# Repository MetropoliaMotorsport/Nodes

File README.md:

# Nodes
New Power + Analog nodes for HPF24

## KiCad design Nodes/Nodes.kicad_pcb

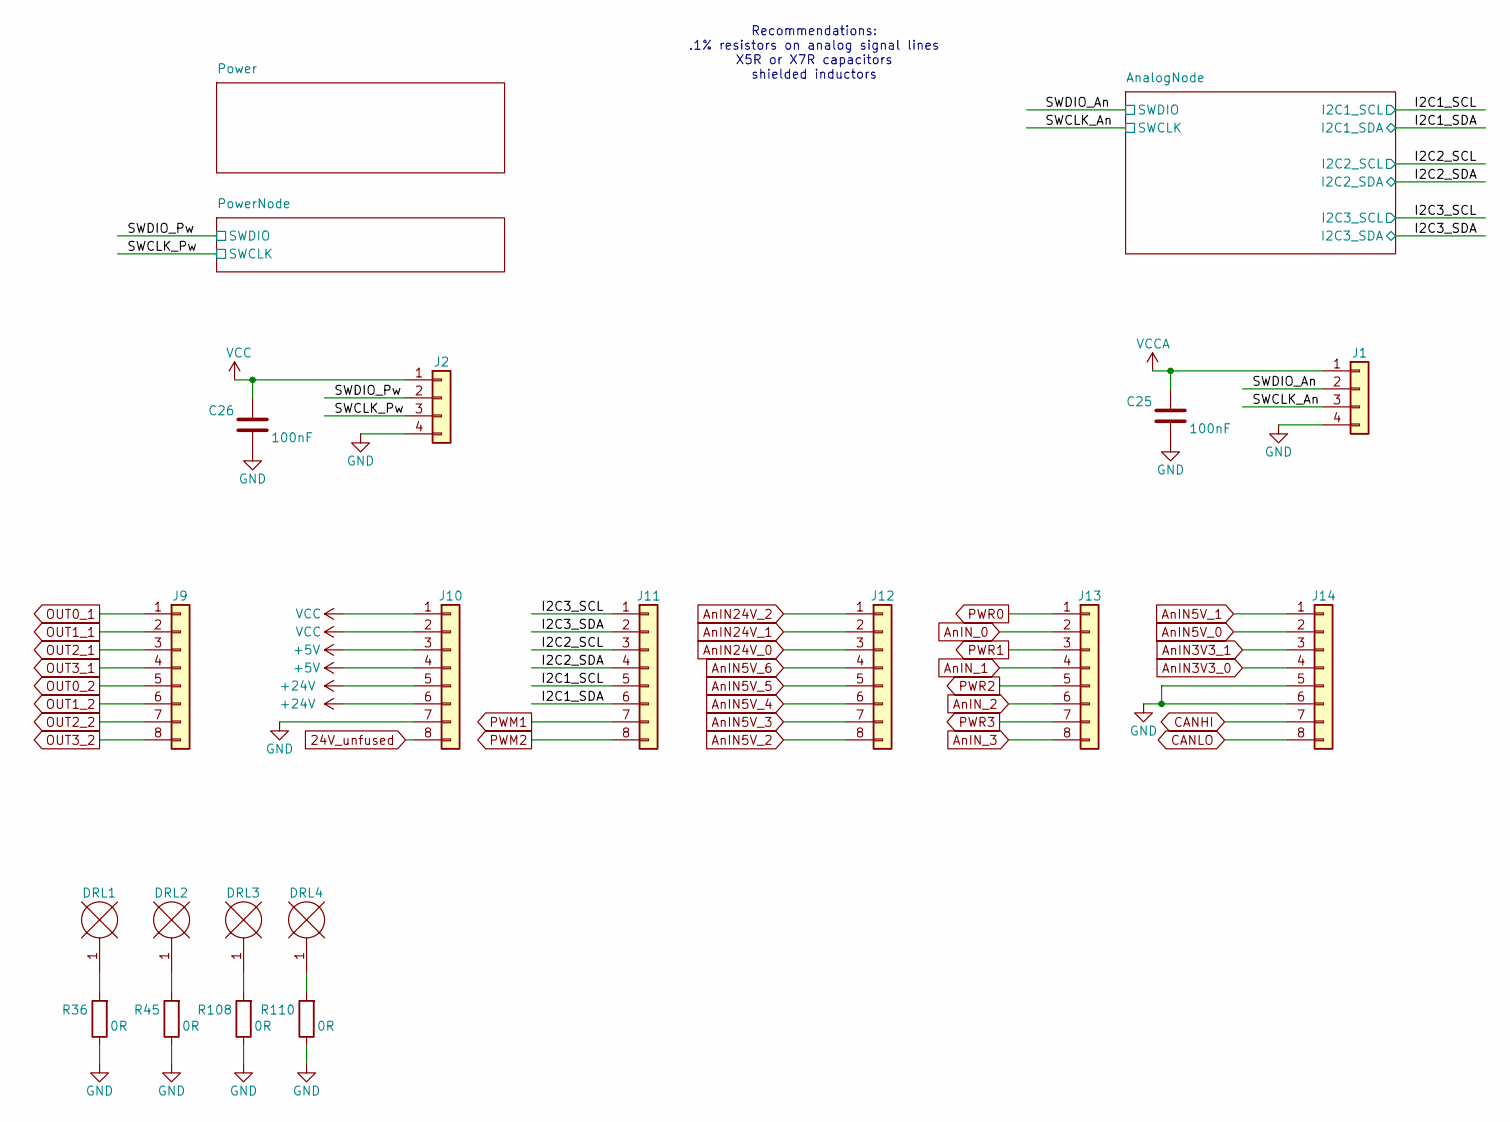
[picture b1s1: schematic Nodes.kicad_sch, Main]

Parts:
C25, C26: 100nF; C_0805_2012Metric_Pad1.18x1.45mm_HandSolder; TOLERANCE (FILL IN AS +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 10%
DRL1, DRL2, DRL3, DRL4: HOLE4.28.4; MountingHole_4.3mm_M4_Pad
J1, J2: Conn_01x04; PinSocket_1x04_P2.54mm_Vertical
J9, J10, J11, J12, J13, J14: Conn_01x08; PinHeader_1x08_P2.54mm_Vertical
R36, R45, R108, R110: 0R; R_0805_2012Metric_Pad1.20x1.40mm_HandSolder

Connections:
24V_unfused: J10.8; also elsewhere on the board
+5V: J10.3, J10.4; also elsewhere on the board
+24V: J10.5, J10.6; also elsewhere on the board
/I2C1_SCL: J11.5; also elsewhere on the board
/I2C1_SDA: J11.6; also elsewhere on the board
/I2C2_SCL: J11.3; also elsewhere on the board
/I2C2_SDA: J11.4; also elsewhere on the board
/I2C3_SCL: J11.1; also elsewhere on the board
/I2C3_SDA: J11.2; also elsewhere on the board
/SWCLK_An: J1.3; also elsewhere on the board
/SWCLK_Pw: J2.3; also elsewhere on the board
/SWDIO_An: J1.2; also elsewhere on the board
/SWDIO_Pw: J2.2; also elsewhere on the board
AnIN3V3_0: J14.4; also elsewhere on the board
AnIN3V3_1: J14.3; also elsewhere on the board
AnIN5V_0: J14.2; also elsewhere on the board
AnIN5V_1: J14.1; also elsewhere on the board
AnIN5V_2: J12.8; also elsewhere on the board
AnIN5V_3: J12.7; also elsewhere on the board
AnIN5V_4: J12.6; also elsewhere on the board
AnIN5V_5: J12.5; also elsewhere on the board
AnIN5V_6: J12.4; also elsewhere on the board
AnIN24V_0: J12.3; also elsewhere on the board
AnIN24V_1: J12.2; also elsewhere on the board
AnIN24V_2: J12.1; also elsewhere on the board
AnIN_0: J13.2; also elsewhere on the board
AnIN_1: J13.4; also elsewhere on the board
AnIN_2: J13.6; also elsewhere on the board
AnIN_3: J13.8; also elsewhere on the board
CANHI: J14.7; also elsewhere on the board
CANLO: J14.8; also elsewhere on the board
GND: C25.2, C26.2, J1.4, J2.4, J10.7, J14.5, J14.6, R36.1, R45.1, R108.1, R110.1; also elsewhere on the board
unnamed: DRL1.1, R36.2
unnamed: DRL2.1, R45.2
unnamed: DRL3.1, R108.2
unnamed: DRL4.1, R110.2
OUT0_1: J9.1; also elsewhere on the board
OUT0_2: J9.5; also elsewhere on the board
OUT1_1: J9.2; also elsewhere on the board
OUT1_2: J9.6; also elsewhere on the board
OUT2_1: J9.3; also elsewhere on the board
OUT2_2: J9.7; also elsewhere on the board
OUT3_1: J9.4; also elsewhere on the board
OUT3_2: J9.8; also elsewhere on the board
PWM1: J11.7; also elsewhere on the board
PWM2: J11.8; also elsewhere on the board
PWR0: J13.1; also elsewhere on the board
PWR1: J13.3; also elsewhere on the board
PWR2: J13.5; also elsewhere on the board
PWR3: J13.7; also elsewhere on the board
VCC: C26.1, J2.1, J10.1, J10.2; also elsewhere on the board
VCCA: C25.1, J1.1; also elsewhere on the board

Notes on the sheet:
Recommendations: .1% resistors on analog signal lines X5R or X7R capacitors shielded inductors
${REVISION}

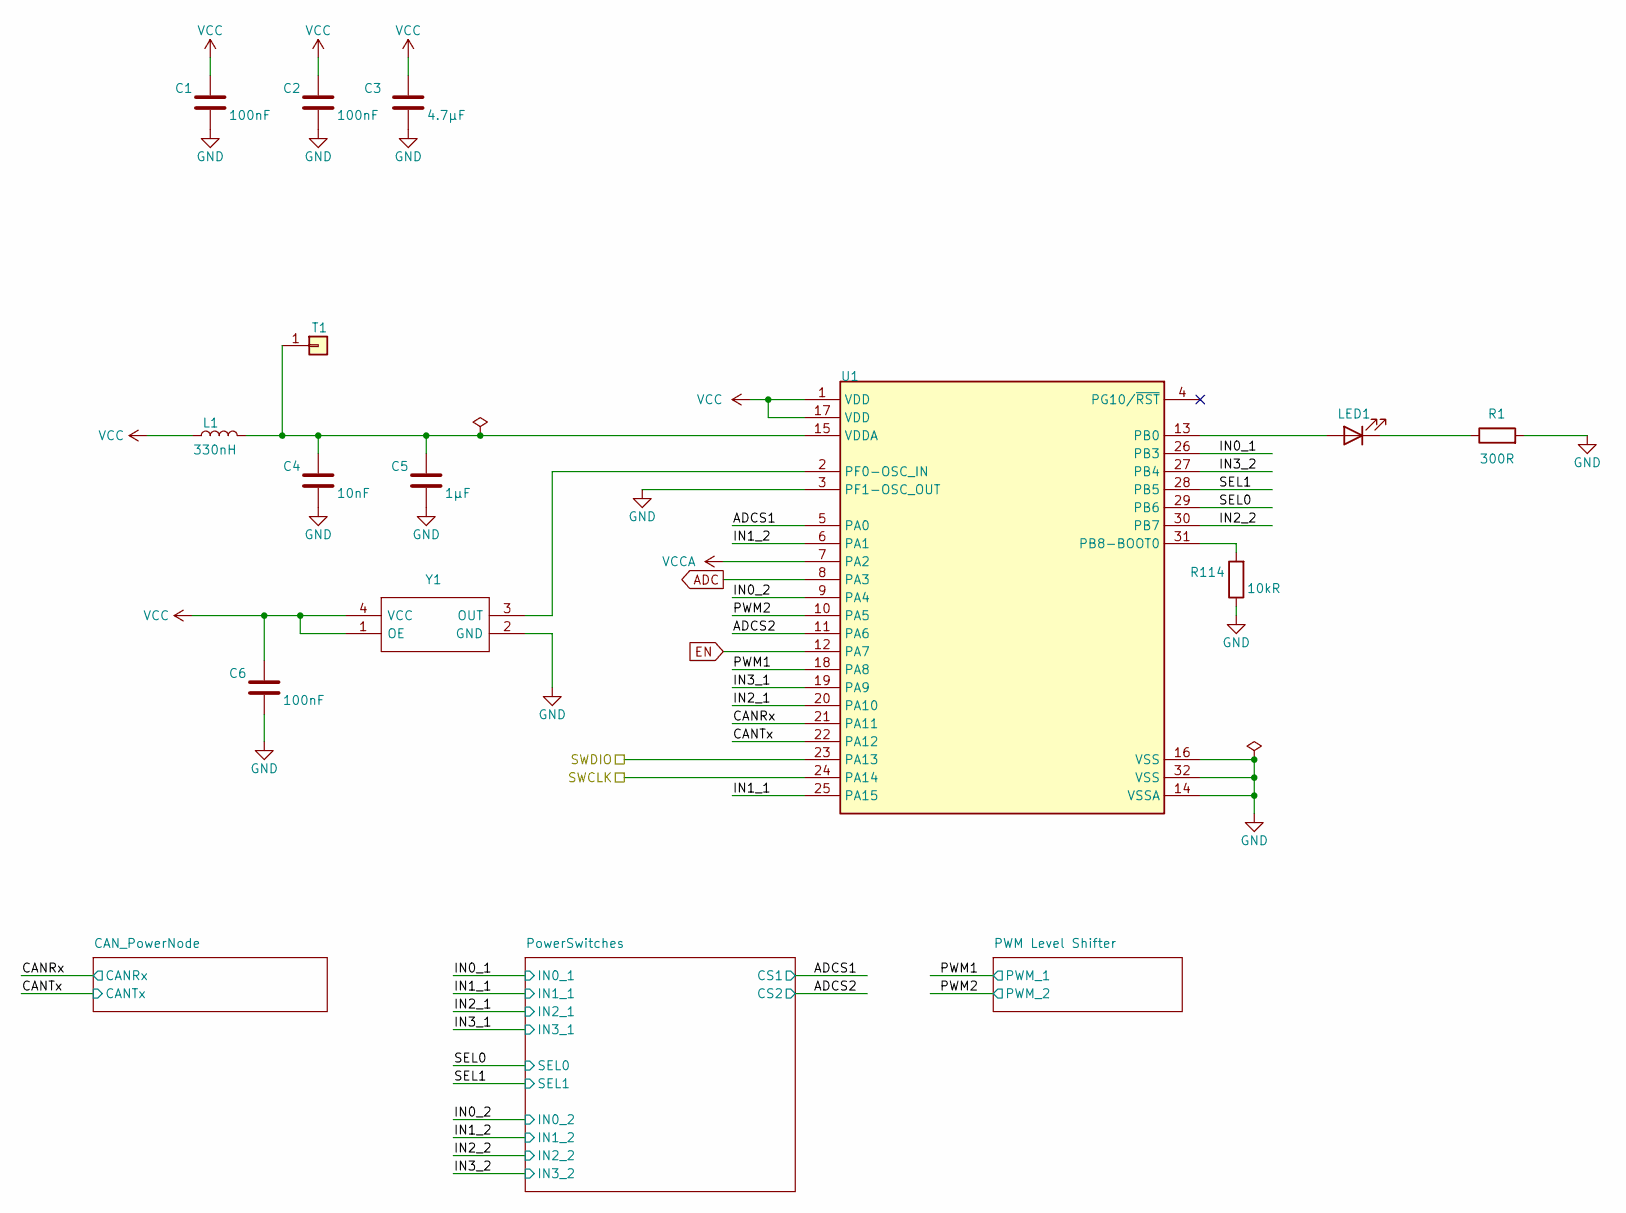
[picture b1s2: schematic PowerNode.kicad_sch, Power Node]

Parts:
C1, C2, C6: 100nF; C_0805_2012Metric_Pad1.18x1.45mm_HandSolder; TOLERANCE (FILL IN AS +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 10%
C3: 4.7µF; C_0805_2012Metric_Pad1.18x1.45mm_HandSolder; TOLERANCE (FILL IN AS +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 10%
C4: 10nF; C_0805_2012Metric_Pad1.18x1.45mm_HandSolder; TOLERANCE (FILL IN AS +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 10%
C5: 1µF; C_0805_2012Metric_Pad1.18x1.45mm_HandSolder; TOLERANCE (FILL IN AS +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 10%
L1: 330nH; L_0805_2012Metric_Pad1.15x1.40mm_HandSolder; TOLERANCE 20%
LED1: SML-210VTT86; LED_0805_2012Metric_Pad1.15x1.40mm_HandSolder; FORWARD VOLTAGE 2V; REVERSE VOLTAGE 4V; MANUFACTURER PART NUMBER SML-210VTT86; MOUSER DESCRIPTION Standard LEDs - SMD RED SMD TRANS LENS
R1: 300R; R_0805_2012Metric_Pad1.20x1.40mm_HandSolder; POWER RATING 400mW; TOLERANCE 5%
R114: 10kR; R_0805_2012Metric_Pad1.20x1.40mm_HandSolder
T1: Conn_01x01; TestPoint_THTPad_D1.5mm_Drill0.7mm
U1: STM32G431KBT6; FP-LQFP32-5V-IPC_B
Y1: SG-8018CE_8.0000M-TJHPA3; SG8018CE80000MTJHPA3; Mouser Part Number 732-CE8M-TJHPA3

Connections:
/PowerNode/ADCS1: U1.5 (PA0); also elsewhere on the board
/PowerNode/ADCS2: U1.11 (PA6); also elsewhere on the board
/PowerNode/CANRx: U1.21 (PA11); also elsewhere on the board
/PowerNode/CANTx: U1.22 (PA12); also elsewhere on the board
/PowerNode/IN0_1: U1.26 (PB3); also elsewhere on the board
/PowerNode/IN0_2: U1.9 (PA4); also elsewhere on the board
/PowerNode/IN1_1: U1.25 (PA15); also elsewhere on the board
/PowerNode/IN1_2: U1.6 (PA1); also elsewhere on the board
/PowerNode/IN2_1: U1.20 (PA10); also elsewhere on the board
/PowerNode/IN2_2: U1.30 (PB7); also elsewhere on the board
/PowerNode/IN3_1: U1.19 (PA9); also elsewhere on the board
/PowerNode/IN3_2: U1.27 (PB4); also elsewhere on the board
/PowerNode/PWM1: U1.18 (PA8); also elsewhere on the board
/PowerNode/PWM2: U1.10 (PA5); also elsewhere on the board
/PowerNode/SEL0: U1.29 (PB6); also elsewhere on the board
/PowerNode/SEL1: U1.28 (PB5); also elsewhere on the board
/SWCLK_Pw: U1.24 (PA14); also elsewhere on the board
/SWDIO_Pw: U1.23 (PA13); also elsewhere on the board
ADC: U1.8 (PA3); also elsewhere on the board
EN: U1.12 (PA7); also elsewhere on the board
GND: C1.2, C2.2, C3.2, C4.2, C5.2, C6.2, R1.2, R114.1, U1.3 (PF1-OSC_OUT), U1.14 (VSSA), U1.16 (VSS), U1.32 (VSS), Y1.2 (GND); also elsewhere on the board
unnamed: LED1.2 (A), U1.13 (PB0)
unnamed: LED1.1 (K), R1.1
unnamed: C4.1, C5.1, L1.2, T1.1, U1.15 (VDDA)
unnamed: R114.2, U1.31 (PB8-BOOT0)
unnamed: U1.2 (PF0-OSC_IN), Y1.3 (OUT)
VCC: C1.1, C2.1, C3.1, C6.1, L1.1, U1.1 (VDD), U1.17 (VDD), Y1.1 (OE), Y1.4 (VCC); also elsewhere on the board
VCCA: U1.7 (PA2); also elsewhere on the board

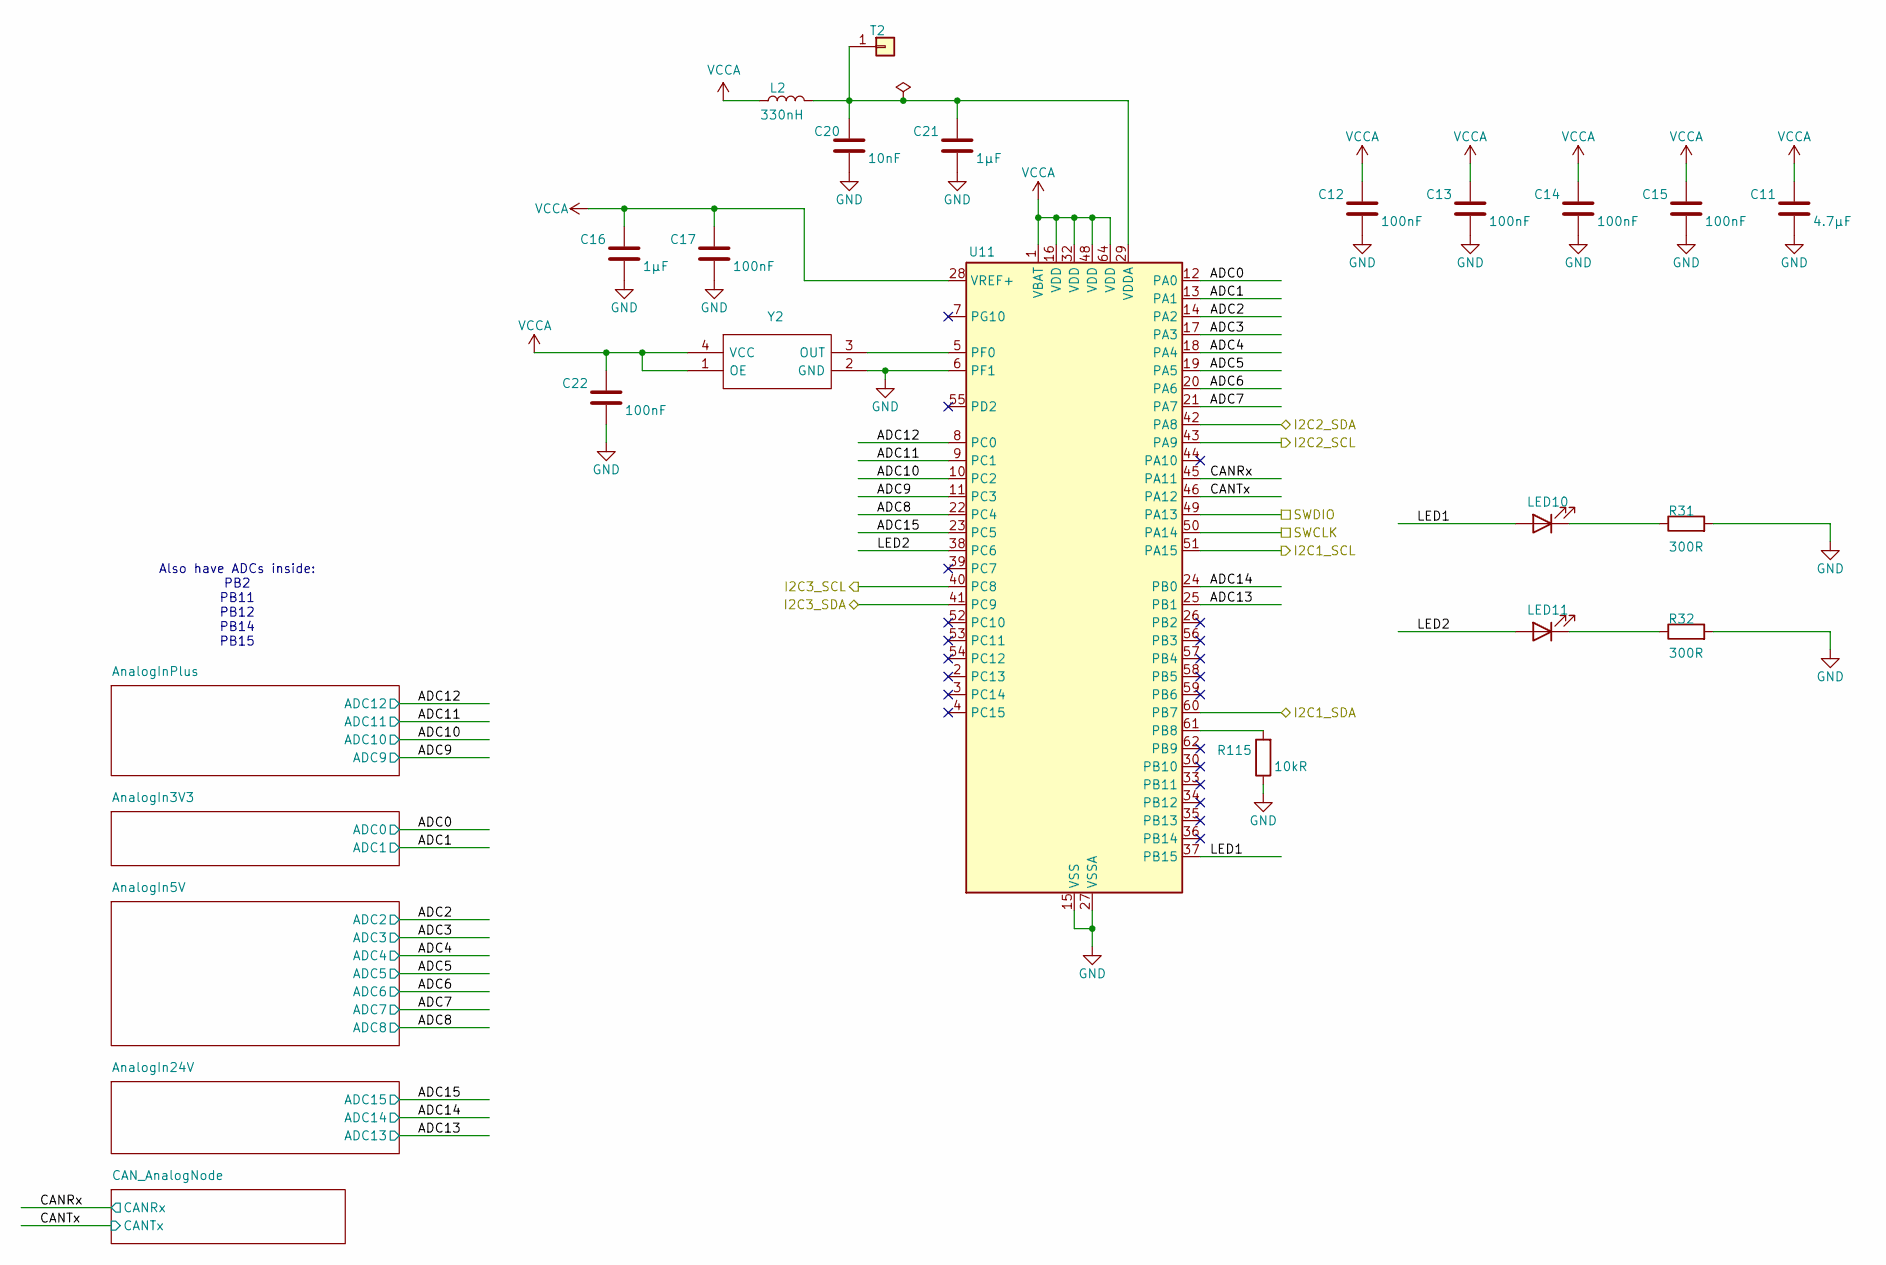
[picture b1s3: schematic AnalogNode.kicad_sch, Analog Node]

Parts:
C11: 4.7µF; C_0805_2012Metric_Pad1.18x1.45mm_HandSolder; TOLERANCE (FILL IN AS +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 10%
C12, C13, C14, C15, C17, C22: 100nF; C_0805_2012Metric_Pad1.18x1.45mm_HandSolder; TOLERANCE (FILL IN AS +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 10%
C16, C21: 1µF; C_0805_2012Metric_Pad1.18x1.45mm_HandSolder; TOLERANCE (FILL IN AS +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 10%
C20: 10nF; C_0805_2012Metric_Pad1.18x1.45mm_HandSolder; TOLERANCE (FILL IN AS +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 10%
L2: 330nH; L_0805_2012Metric_Pad1.15x1.40mm_HandSolder; TOLERANCE 20%
LED10, LED11: SML-210VTT86; LED_0805_2012Metric_Pad1.15x1.40mm_HandSolder; FORWARD VOLTAGE 2V; REVERSE VOLTAGE 4V; MANUFACTURER PART NUMBER SML-210VTT86; MOUSER DESCRIPTION Standard LEDs - SMD RED SMD TRANS LENS
R31, R32: 300R; R_0805_2012Metric_Pad1.20x1.40mm_HandSolder; POWER RATING 400mW; TOLERANCE 5%
R115: 10kR; R_0805_2012Metric_Pad1.20x1.40mm_HandSolder
T2: Conn_01x01; TestPoint_THTPad_D1.5mm_Drill0.7mm
U11: STM32G431RBTx; LQFP-64_10x10mm_P0.5mm
Y2: SG-8018CE_8.0000M-TJHPA3; SG8018CE80000MTJHPA3; Mouser Part Number 732-CE8M-TJHPA3

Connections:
/AnalogNode/ADC0: U11.12 (PA0); also elsewhere on the board
/AnalogNode/ADC1: U11.13 (PA1); also elsewhere on the board
/AnalogNode/ADC2: U11.14 (PA2); also elsewhere on the board
/AnalogNode/ADC3: U11.17 (PA3); also elsewhere on the board
/AnalogNode/ADC4: U11.18 (PA4); also elsewhere on the board
/AnalogNode/ADC5: U11.19 (PA5); also elsewhere on the board
/AnalogNode/ADC6: U11.20 (PA6); also elsewhere on the board
/AnalogNode/ADC7: U11.21 (PA7); also elsewhere on the board
/AnalogNode/ADC8: U11.22 (PC4); also elsewhere on the board
/AnalogNode/ADC9: U11.11 (PC3); also elsewhere on the board
/AnalogNode/ADC10: U11.10 (PC2); also elsewhere on the board
/AnalogNode/ADC11: U11.9 (PC1); also elsewhere on the board
/AnalogNode/ADC12: U11.8 (PC0); also elsewhere on the board
/AnalogNode/ADC13: U11.25 (PB1); also elsewhere on the board
/AnalogNode/ADC14: U11.24 (PB0); also elsewhere on the board
/AnalogNode/ADC15: U11.23 (PC5); also elsewhere on the board
/AnalogNode/CANRx: U11.45 (PA11); also elsewhere on the board
/AnalogNode/CANTx: U11.46 (PA12); also elsewhere on the board
/AnalogNode/LED1: LED10.2 (A), U11.37 (PB15)
/AnalogNode/LED2: LED11.2 (A), U11.38 (PC6)
/I2C1_SCL: U11.51 (PA15); also elsewhere on the board
/I2C1_SDA: U11.60 (PB7); also elsewhere on the board
/I2C2_SCL: U11.43 (PA9); also elsewhere on the board
/I2C2_SDA: U11.42 (PA8); also elsewhere on the board
/I2C3_SCL: U11.40 (PC8); also elsewhere on the board
/I2C3_SDA: U11.41 (PC9); also elsewhere on the board
/SWCLK_An: U11.50 (PA14); also elsewhere on the board
/SWDIO_An: U11.49 (PA13); also elsewhere on the board
GND: C11.2, C12.2, C13.2, C14.2, C15.2, C16.2, C17.2, C20.2, C21.2, C22.2, R31.2, R32.2, R115.1, U11.6 (PF1), U11.15 (VSS), U11.27 (VSSA), U11.31 (VSS), U11.47 (VSS), U11.63 (VSS), Y2.2 (GND); also elsewhere on the board
unnamed: LED10.1 (K), R31.1
unnamed: LED11.1 (K), R32.1
unnamed: C20.1, C21.1, L2.2, T2.1, U11.29 (VDDA)
unnamed: R115.2, U11.61 (PB8)
unnamed: U11.5 (PF0), Y2.3 (OUT)
VCCA: C11.1, C12.1, C13.1, C14.1, C15.1, C16.1, C17.1, C22.1, L2.1, U11.1 (VBAT), U11.16 (VDD), U11.28 (VREF+), U11.32 (VDD), U11.48 (VDD), U11.64 (VDD), Y2.1 (OE), Y2.4 (VCC); also elsewhere on the board

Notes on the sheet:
Also have ADCs inside: PB2 PB11 PB12 PB14 PB15

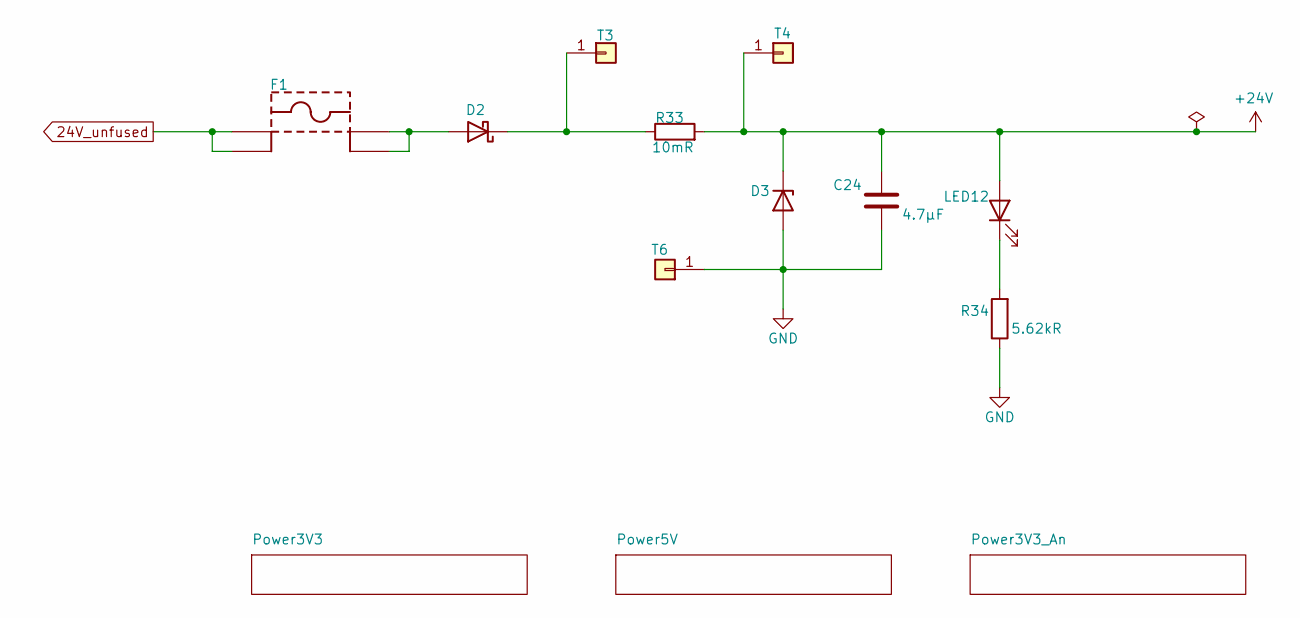
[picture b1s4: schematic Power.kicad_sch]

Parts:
C24: 4.7µF; C_0805_2012Metric_Pad1.18x1.45mm_HandSolder; TOLERANCE (FILL IN AS +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 10%
D2: SX33L_R1_00001; D_SMA_Handsoldering
D3: 1SMA5934BT3G; D_SMA_Handsoldering; PARTNUMBER 1SMA5934BT3G
F1: 3557-2; KSTN-3557-2; VOLTAGE 500V; CURRENT RATING 30A
LED12: SMLMN2WB1CW1; LED_0805_2012Metric_Pad1.15x1.40mm_HandSolder; MANUFACTURER_PART_NUMBER SMLMN2WB1CW1; MOUSER PART NUMBER 755-SMLMN2WB1CW1C
R33: 10mR; R_0805_2012Metric_Pad1.20x1.40mm_HandSolder; TOLERANCE 1%
R34: 5.62kR; R_0805_2012Metric_Pad1.20x1.40mm_HandSolder
T3, T4, T6: Conn_01x01; TestPoint_THTPad_D1.5mm_Drill0.7mm

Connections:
24V_unfused: F1.1, F1.2; also elsewhere on the board
+24V: C24.1, D3.1 (K), LED12.2 (A), R33.2, T4.1; also elsewhere on the board
GND: C24.2, D3.2 (A), R34.1, T6.1; also elsewhere on the board
unnamed: D2.2 (A), F1.3, F1.4
unnamed: D2.1 (K), R33.1, T3.1
unnamed: LED12.1 (K), R34.2

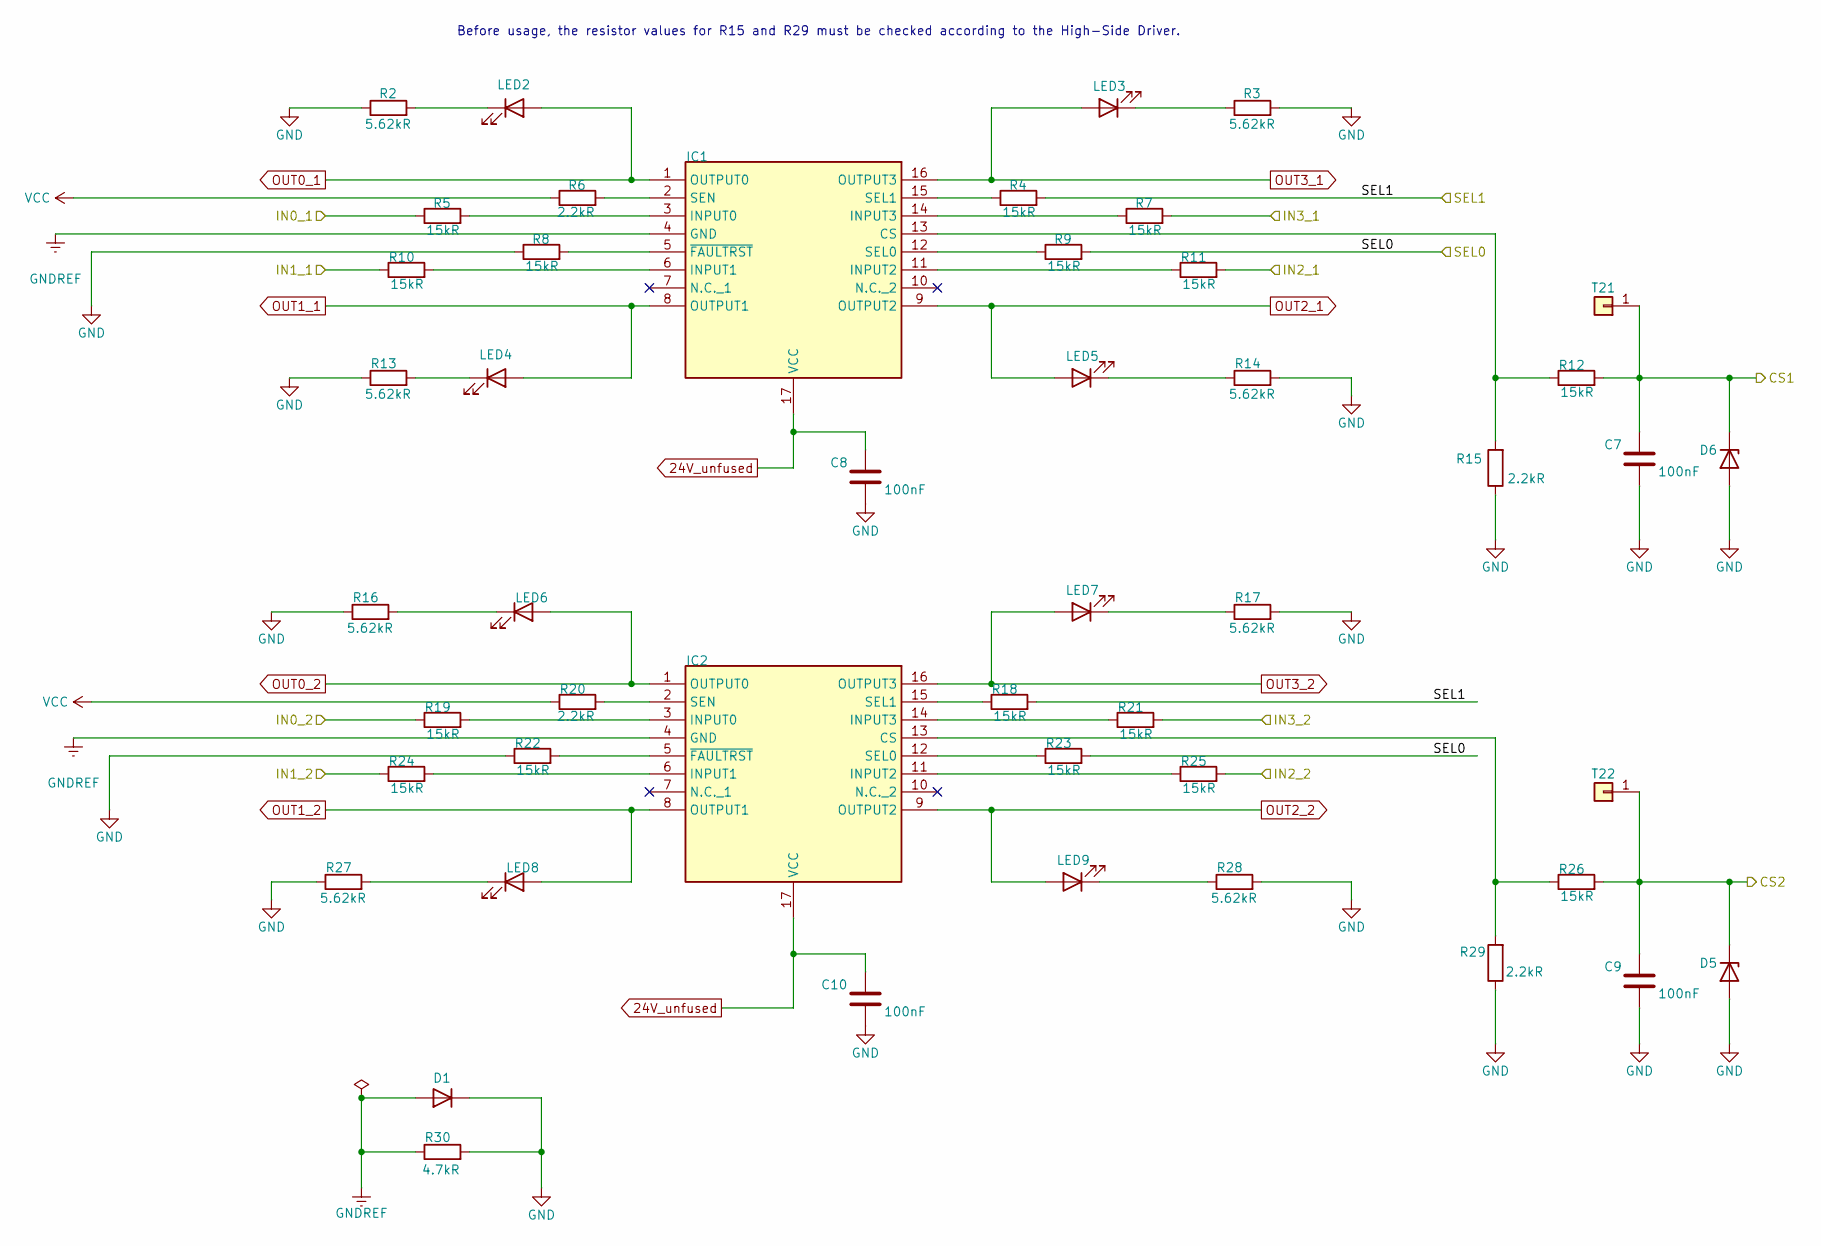
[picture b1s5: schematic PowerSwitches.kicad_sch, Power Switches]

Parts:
C7, C8, C9, C10: 100nF; C_0805_2012Metric_Pad1.18x1.45mm_HandSolder; TOLERANCE (FILL IN AS +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 10%
D1: S1M-13-F; D_SMA_Handsoldering; FORWARD VOLTAGE 1.1V
D5, D6: 1SMA5913BT3G; D_SMA_Handsoldering
IC1, IC2: VNQ9025AJTR; SOP50P600X170-17N; MANUFACTURER_PART_NUMBER VNQ9025AJTR; MOUSER PART NUMBER 511-VNQ9025AJTR
LED2, LED6: SML-H12D8TT86; LED_0805_2012Metric_Pad1.15x1.40mm_HandSolder; MANUFACTURER_PART_NUMBER SML-H12D8TT86; MOUSER PART NUMBER 755-SML-H12D8TT86
LED3, LED7: 150080BS75000; LED_0805_2012Metric_Pad1.15x1.40mm_HandSolder; MANUFACTURER_PART_NUMBER SZYY0805B
LED4, LED8: SML-210YTT86M; LED_0805_2012Metric_Pad1.15x1.40mm_HandSolder; MANUFACTURER_PART_NUMBER SML-210YTT86M
LED5, LED9: SML-H12P8TT86; LED_0805_2012Metric_Pad1.15x1.40mm_HandSolder; MANUFACTURER_PART_NUMBER SML-H12P8TT86; MOUSER PART NUMBER 755-SML-H12P8TT86
R2, R3, R13, R14, R16, R17, R27, R28: 5.62kR; R_0805_2012Metric_Pad1.20x1.40mm_HandSolder
R4, R5, R7, R8, R9, R10, R11, R12, R18, R19, R21, R22, R23, R24, R25, R26: 15kR; R_0805_2012Metric_Pad1.20x1.40mm_HandSolder; TOLERANCE 0.25%; WORKING VOLTAGE 150V
R6, R15, R20, R29: 2.2kR; R_0805_2012Metric_Pad1.20x1.40mm_HandSolder; TOLERANCE 1%; WORKING VOLTAGE 150V
R30: 4.7kR; R_0805_2012Metric_Pad1.20x1.40mm_HandSolder; TOLERANCE 0.5%; WORKING VOLTAGE 150V
T21, T22: Conn_01x01; TestPoint_THTPad_D1.5mm_Drill0.7mm

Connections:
24V_unfused: C8.1, C10.1, IC1.17 (VCC), IC2.17 (VCC); also elsewhere on the board
/PowerNode/ADCS1: C7.1, D6.1 (K), R12.2, T21.1; also elsewhere on the board
/PowerNode/ADCS2: C9.1, D5.1 (K), R26.2, T22.1; also elsewhere on the board
/PowerNode/IN0_1: R5.1; also elsewhere on the board
/PowerNode/IN0_2: R19.1; also elsewhere on the board
/PowerNode/IN1_1: R10.1; also elsewhere on the board
/PowerNode/IN1_2: R24.1; also elsewhere on the board
/PowerNode/IN2_1: R11.2; also elsewhere on the board
/PowerNode/IN2_2: R25.2; also elsewhere on the board
/PowerNode/IN3_1: R7.2; also elsewhere on the board
/PowerNode/IN3_2: R21.2; also elsewhere on the board
/PowerNode/SEL0: R9.2, R23.2; also elsewhere on the board
/PowerNode/SEL1: R4.2, R18.2; also elsewhere on the board
GND: C7.2, C8.2, C9.2, C10.2, D1.1 (K), D5.2 (A), D6.2 (A), R2.1, R3.2, R8.1, R13.1, R14.2, R15.1, R16.1, R17.2, R22.1, R27.1, R28.2, R29.1, R30.2; also elsewhere on the board
GNDREF: D1.2 (A), IC1.4 (GND), IC2.4 (GND), R30.1
unnamed: IC1.13 (CS), R12.1, R15.2
unnamed: IC1.3 (INPUT0), R5.2
unnamed: IC1.6 (INPUT1), R10.2
unnamed: IC1.11 (INPUT2), R11.1
unnamed: IC1.14 (INPUT3), R7.1
unnamed: IC1.12 (SEL0), R9.1
unnamed: IC1.15 (SEL1), R4.1
unnamed: IC1.2 (SEN), R6.2
unnamed: IC1.5 (~FAULTRST), R8.2
unnamed: IC2.13 (CS), R26.1, R29.2
unnamed: IC2.3 (INPUT0), R19.2
unnamed: IC2.6 (INPUT1), R24.2
unnamed: IC2.11 (INPUT2), R25.1
unnamed: IC2.14 (INPUT3), R21.1
unnamed: IC2.12 (SEL0), R23.1
unnamed: IC2.15 (SEL1), R18.1
unnamed: IC2.2 (SEN), R20.2
unnamed: IC2.5 (~FAULTRST), R22.2
unnamed: LED2.1 (K), R2.2
unnamed: LED3.1 (K), R3.1
unnamed: LED4.1 (K), R13.2
unnamed: LED5.1 (K), R14.1
unnamed: LED6.1 (K), R16.2
unnamed: LED7.1 (K), R17.1
unnamed: LED8.1 (K), R27.2
unnamed: LED9.1 (K), R28.1
OUT0_1: IC1.1 (OUTPUT0), LED2.2 (A); also elsewhere on the board
OUT0_2: IC2.1 (OUTPUT0), LED6.2 (A); also elsewhere on the board
OUT1_1: IC1.8 (OUTPUT1), LED4.2 (A); also elsewhere on the board
OUT1_2: IC2.8 (OUTPUT1), LED8.2 (A); also elsewhere on the board
OUT2_1: IC1.9 (OUTPUT2), LED5.2 (A); also elsewhere on the board
OUT2_2: IC2.9 (OUTPUT2), LED9.2 (A); also elsewhere on the board
OUT3_1: IC1.16 (OUTPUT3), LED3.2 (A); also elsewhere on the board
OUT3_2: IC2.16 (OUTPUT3), LED7.2 (A); also elsewhere on the board
VCC: R6.1, R20.1; also elsewhere on the board

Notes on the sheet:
Before usage, the resistor values for R15 and R29 ​​must be checked according to the High-Side Driver.

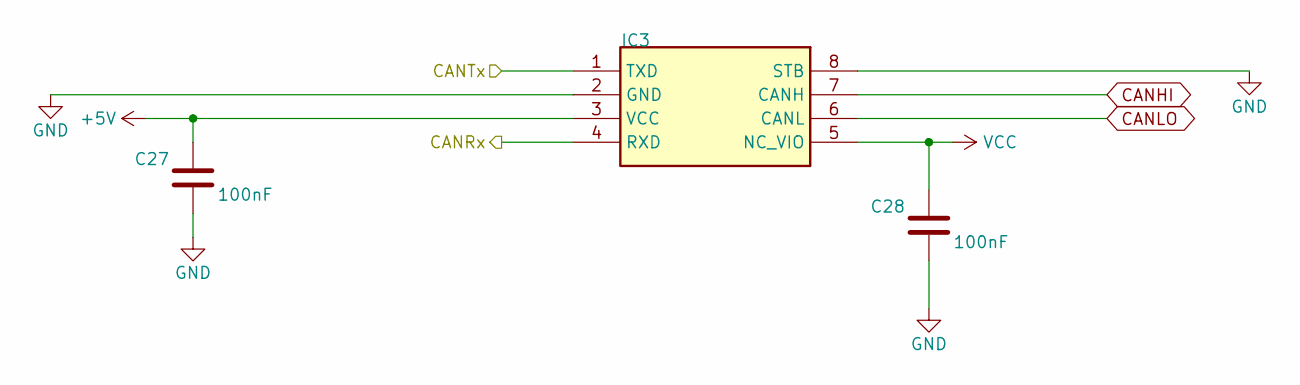
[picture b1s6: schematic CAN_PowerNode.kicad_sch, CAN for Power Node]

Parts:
C27, C28: 100nF; C_0805_2012Metric_Pad1.18x1.45mm_HandSolder; TOLERANCE (FILL IN AS +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 10%
IC3: TCAN1462VDRQ1; SOIC127P600X175-8N; MANUFACTURER_PART_NUMBER TCAN1462VDRQ1; MOUSER PART NUMBER 595-TCAN1462VDRQ1

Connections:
+5V: C27.1, IC3.3 (VCC); also elsewhere on the board
/PowerNode/CANRx: IC3.4 (RXD); also elsewhere on the board
/PowerNode/CANTx: IC3.1 (TXD); also elsewhere on the board
CANHI: IC3.7 (CANH); also elsewhere on the board
CANLO: IC3.6 (CANL); also elsewhere on the board
GND: C27.2, C28.2, IC3.2 (GND), IC3.8 (STB); also elsewhere on the board
VCC: C28.1, IC3.5 (NC_VIO); also elsewhere on the board

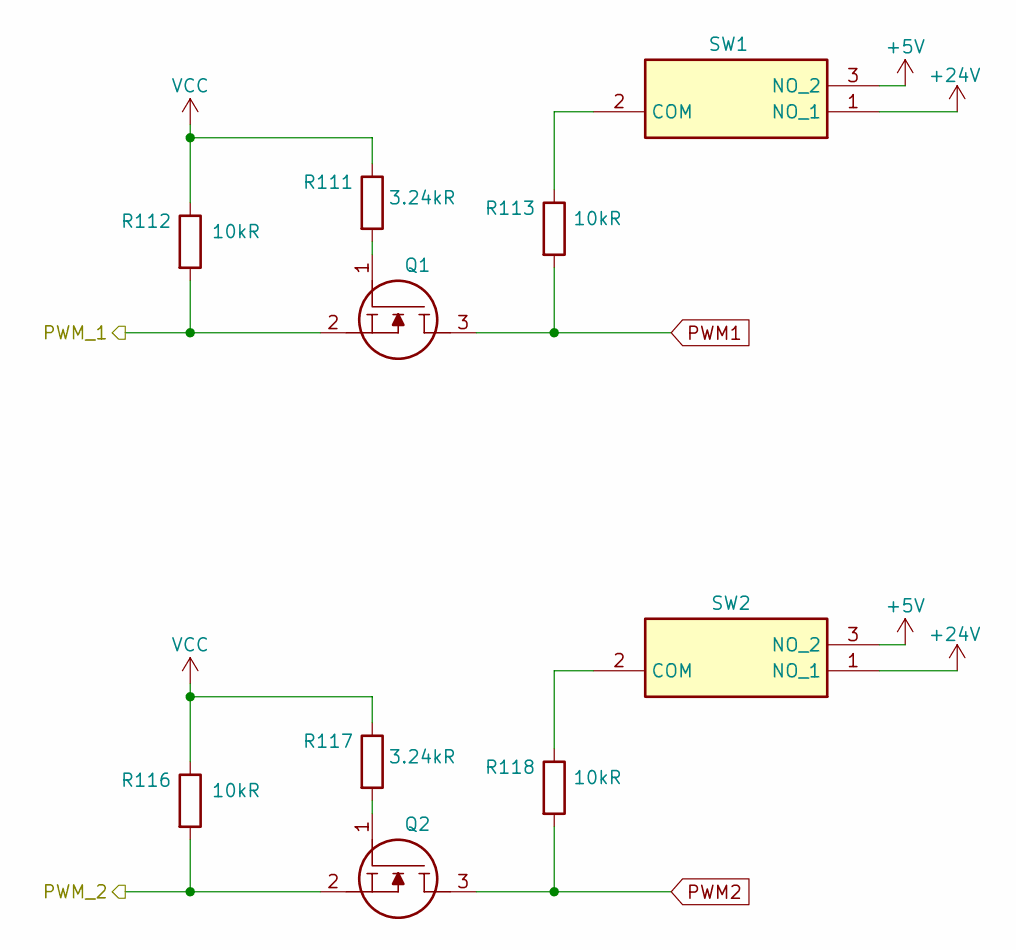
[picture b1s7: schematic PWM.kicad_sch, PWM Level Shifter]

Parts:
Q1, Q2: TN2106K1-G; SOT95P237X112-3N; Mouser Part Number 689-TN2106K1-G
R111, R117: 3.24kR; R_0805_2012Metric_Pad1.20x1.40mm_HandSolder
R112, R113, R116, R118: 10kR; R_0805_2012Metric_Pad1.20x1.40mm_HandSolder
SW1, SW2: CJS-1201TB1; CJS1201TB1; Mouser Part Number 229-CJS-1201TB1

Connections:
+5V: SW1.3 (NO_2), SW2.3 (NO_2); also elsewhere on the board
+24V: SW1.1 (NO_1), SW2.1 (NO_1); also elsewhere on the board
/PowerNode/PWM1: Q1.2, R112.2; also elsewhere on the board
/PowerNode/PWM2: Q2.2, R116.2; also elsewhere on the board
unnamed: Q1.1, R111.2
unnamed: Q2.1, R117.2
unnamed: R113.1, SW1.2 (COM)
unnamed: R118.1, SW2.2 (COM)
PWM1: Q1.3, R113.2; also elsewhere on the board
PWM2: Q2.3, R118.2; also elsewhere on the board
VCC: R111.1, R112.1, R116.1, R117.1; also elsewhere on the board

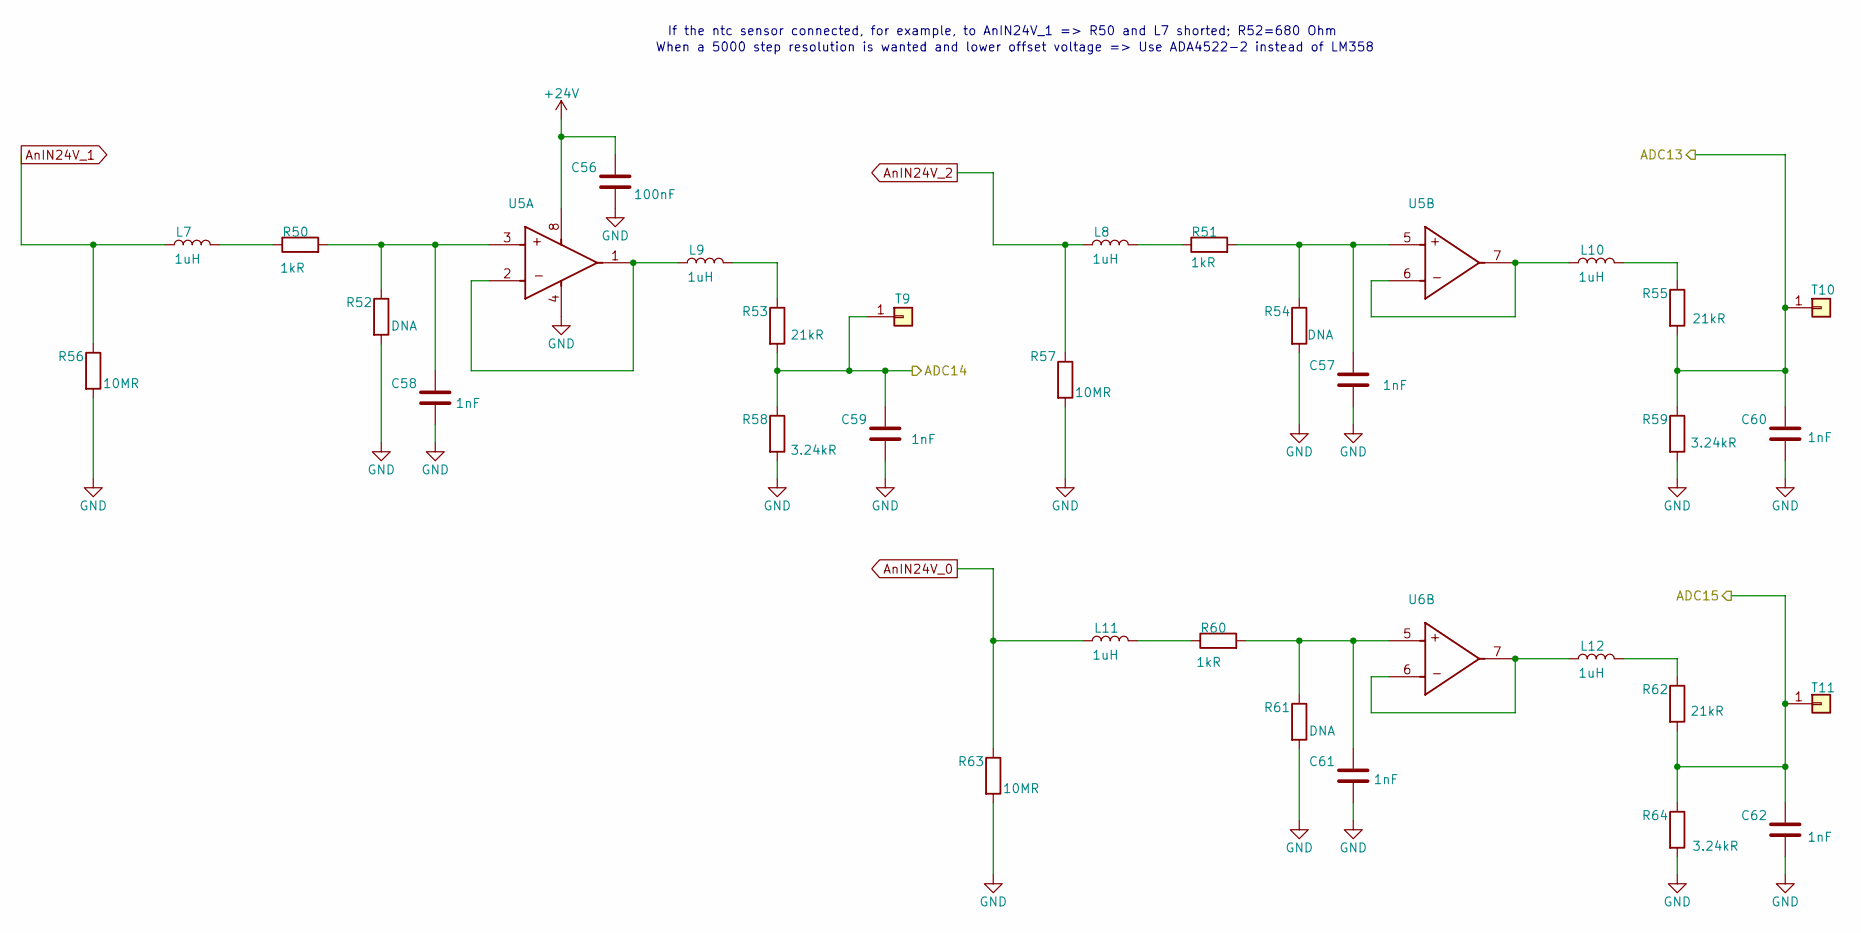
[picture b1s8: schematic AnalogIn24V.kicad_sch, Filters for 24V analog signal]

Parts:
C56: 100nF; C_0805_2012Metric_Pad1.18x1.45mm_HandSolder; TOLERANCE (FILL IN AS +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 10%
C57, C58, C59, C60, C61, C62: 1nF; C_0805_2012Metric_Pad1.18x1.45mm_HandSolder
L7, L8, L9, L10, L11, L12: 1uH; L_0805_2012Metric_Pad1.15x1.40mm_HandSolder; TOLERANCE 30%; CURRENT RATING 900mA
R50, R51, R60: 1kR; R_0805_2012Metric_Pad1.20x1.40mm_HandSolder
R52, R54, R61: DNA; R_0805_2012Metric_Pad1.20x1.40mm_HandSolder; PART NUMBER CRCW0805680RFKEA
R53, R55, R62: 21kR; R_0805_2012Metric_Pad1.20x1.40mm_HandSolder
R56, R57, R63: 10MR; R_0805_2012Metric_Pad1.20x1.40mm_HandSolder; POWER RATING 125mW; VOLTAGE RATING (DC) 150V
R58, R59, R64: 3.24kR; R_0805_2012Metric_Pad1.20x1.40mm_HandSolder
T9, T10, T11: Conn_01x01; TestPoint_THTPad_D1.5mm_Drill0.7mm
U5, U6: LM358BAIDR; FP-D0008A-IPC_A

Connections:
+24V: C56.1, U5.8 (V+); also elsewhere on the board
/AnalogNode/ADC13: C60.1, R55.2, R59.1, T10.1; also elsewhere on the board
/AnalogNode/ADC14: C59.1, R53.2, R58.1, T9.1; also elsewhere on the board
/AnalogNode/ADC15: C62.1, R62.2, R64.1, T11.1; also elsewhere on the board
AnIN24V_0: L11.1, R63.1; also elsewhere on the board
AnIN24V_1: L7.1, R56.1; also elsewhere on the board
AnIN24V_2: L8.1, R57.1; also elsewhere on the board
GND: C56.2, C57.2, C58.2, C59.2, C60.2, C61.2, C62.2, R52.2, R54.2, R56.2, R57.2, R58.2, R59.2, R61.2, R63.2, R64.2, U5.4 (V-); also elsewhere on the board
unnamed: L7.2, R50.1
unnamed: L8.2, R51.1
unnamed: L9.2, R53.1
unnamed: L10.2, R55.1
unnamed: L11.2, R60.1
unnamed: L12.2, R62.1
unnamed: C58.1, R50.2, R52.1, U5.3 (IN1+)
unnamed: L9.1, U5.1 (OUT1), U5.2 (IN1-)
unnamed: C57.1, R51.2, R54.1, U5.5 (IN2+)
unnamed: L10.1, U5.6 (IN2-), U5.7 (OUT2)
unnamed: C61.1, R60.2, R61.1, U6.5 (IN2+)
unnamed: L12.1, U6.6 (IN2-), U6.7 (OUT2)

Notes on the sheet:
When a 5000 step resolution is wanted and lower offset voltage => Use ADA4522-2 instead of LM358
If the ntc sensor connected, for example, to AnIN24V_1 => R50 and L7 shorted; R52=680 Ohm
